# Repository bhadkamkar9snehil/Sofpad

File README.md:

# Sofpad

**A wireless, split-layout mechanical keyboard in one piece: two Sofle RGB boards in an Alice-style tilted case, with a trackpad between the thumbs, one screen and one battery.**

## What it is

Sofpad is a keyboard for the sofa and the desk. Two original [Sofle RGB](https://github.com/josefadamcik/SofleKeyboard) PCBs sit in a single printed shell, each tilted 12° like an Alice keyboard, so your hands rest naturally and the keyboard stays one object you can carry and lay on your lap. Between the thumb clusters sits a large trackpad that either thumb reaches, so the mouse never needs a separate hand movement.

One controller scans both halves. It talks to the computer over **USB-C cable or Bluetooth**, your choice at any time. The case is designed to look at home in a living room, and to be clean and serviceable on the inside: everything except the key boards rides on one removable plate.

## Features

| | |
|---|---|
| **Layout** | Sofle RGB, 30 keys per half, tilted 12° per half in an Alice-style plan, flat vertically |
| **Switches** | Cherry MX style, hot-swap |
| **Pointing** | Azoteq TPS65 trackpad, 65 × 49 mm, centre front between the thumbs |
| **Controls** | Two rotary encoders |
| **Screen** | One 2.0 in IPS display (centre rear) replaces the two small OLEDs |
| **Connectivity** | USB-C HID and Bluetooth LE HID, both always available |
| **Feel** | Haptic feedback on the trackpad (DRV2605L + LRA) |
| **Power** | One protected 1100 mAh LiPo, USB-C charging, power switch, wake on lift (LIS3DH) |
| **Controller** | One nRF52840 carrier board; the two original Pro Micro boards are removed |
| **Case** | 383 × 153 × 17.1 mm printed shell, one set of screws opens it, no paint |
| **Software** | ZMK firmware. No PC app is ever required |

## Status

Hardware design is complete and being finished for ordering. Nothing is built or tested yet.

| Area | State |
|---|---|
| Case CAD | Done. Automated checks pass: no part overlaps, everything fits its cavity, shell and plate are single solids, meshes are closed |
| Schematics | Carrier and both adapters generated, ERC clean |
| PCB layout | Carrier and both adapters routed. DRC: 0 errors, 0 unconnected |
| Verification without hardware | Schematic, layout and generator netlists agree. Every key, encoder and ground path traced from the Sofle PCB to the nRF52840 GPIO. Power, divider and bus values checked against datasheet formulas. See [ARCHITECTURE.md](hardware/r3/ARCHITECTURE.md) |
| Bill of materials | Done, India sourcing, about ₹5,156 in parts (some prices are estimates) |
| Fabrication | Fab files exported for the carrier and both adapters (`hardware/r3/pcb/fab`). Quotes and orders not placed |
| Firmware | Not started (ZMK) |
| Bench test | Months away, after hardware is ordered and built |

This is a development project, not a tested product.

## Gallery

Keycaps, knobs, battery, carrier and trackpad are fit-check envelopes. The shell, PCB outlines, key positions and mount holes are real geometry. Renders are in [docs/images](docs/images/).

## How it works

```mermaid
flowchart TB
  subgraph CASE["One-piece Sofpad enclosure"]
    L["Left Sofle RGB PCB<br/>30 keys + encoder"] --> A["Left adapter"]
    R["Right Sofle RGB PCB<br/>30 keys + encoder"] --> B["Right adapter"]
    A -->|"16-pin FFC"| MCU["nRF52840 carrier PCB"]
    B -->|"16-pin FFC"| MCU
    PAD["Azoteq TPS65 trackpad"] -->|"I2C"| MCU
    SCR["2.0 in IPS screen"] -->|"SPI"| MCU
    CELL["Protected LiPo"] --> PWR["Charger + 3.3 V buck"]
    USBC["USB-C"] --> PWR
    PWR --> MCU
  end
  MCU -->|"USB HID"| HOST["Computer"]
  MCU -.->|"BLE HID"| HOST
```

Each Sofle half keeps its keys, diodes and encoder. A small adapter solders into the old Pro Micro position and brings the matrix out on a 16-way flat cable to the single carrier board, which holds the MCU, charger, regulator, haptics driver, accelerometer and the screen and trackpad connectors. Power follows the sleep design in [ARCHITECTURE.md](hardware/r3/ARCHITECTURE.md): idle current of a few microamps, wake on key press or lift.

## Repository guide

| You want | Go to |
|---|---|
| Engineering specification | [hardware/r3/ARCHITECTURE.md](hardware/r3/ARCHITECTURE.md) |
| Parts and prices | [BOM.md](hardware/r3/BOM.md) · [BOM.csv](hardware/r3/BOM.csv) |
| PCB sources and fab export | [hardware/r3/pcb](hardware/r3/pcb/) (`carrier.py`, `adapter.py`, `build_pcb.py`, `fab_export.py`) |
| Case CAD and checks | [cad/r3](cad/r3/): [Sofpad_R3_Alice.scad](cad/r3/Sofpad_R3_Alice.scad), `check_design.py`, [DESIGN_RULES.md](cad/r3/DESIGN_RULES.md) |
| Renders | [docs/images](docs/images/) |
| Earlier concepts | [R1](cad/r1/), [R2](cad/r2/), [original source package](archives/Sofpad_All_Source_Files.zip) |

### Build it

Tools: OpenSCAD nightly (Manifold backend), KiCad 10, Freerouting 2.5 with Java 25, Blender 5.

```text
python cad/r3/check_design.py                  case checks, must print PASS
python hardware/r3/pcb/erc.py carrier          schematic check
python hardware/r3/pcb/build_pcb.py carrier    place and route (KiCad's Python)
python hardware/r3/pcb/drc.py carrier carrier  design rule check
python hardware/r3/pcb/fab_export.py carrier carrier   Gerbers, drill, placement, BOM, zip
```

Order settings (layers, mask, finish, assembly) are in the Manufacturing section of [ARCHITECTURE.md](hardware/r3/ARCHITECTURE.md). The case prints in one piece on a large FDM printer, unpainted.

## Remaining work

1. Collect quotes (JLCPCB and Indian fabs) from the exported fab files, then order boards and case.
2. Print a small fit-test piece, then the full shell.
3. Confirm the trackpad flex pitch when the part arrives (both breakout boards are on the BOM).
4. Firmware: ZMK board definition, matrix, encoders, USB and Bluetooth, trackpad gestures, haptics, wake on lift, screen.
5. Deferred: hinged tenting lift, host data on the screen over Bluetooth, over-the-air updates, optional PC companion app.

## History and source integrity

R1 (couch case) and R2 (TPS43 unibody) are kept as earlier concepts. The original ZIP is the authoritative source package: a manual file upload once flattened its folders and left 14 zero-byte files, so use the archive when you need an exact original.

## License

The Sofle RGB PCB is licensed by its author, see [LICENSE-SOFLE.txt](LICENSE-SOFLE.txt). Project license: [LICENSE](LICENSE).

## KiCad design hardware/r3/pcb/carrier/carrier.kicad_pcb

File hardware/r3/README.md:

# Sofle RGB couch keyboard — single nRF52840, single battery, Azoteq TPS65 I2C

Engineering package R3 · 9 November 2026

## What is designed

- Both original Sofle RGB PCB halves remain in one printed upper shell.
- Both existing ATmega32U4 Pro Micro boards are removed. Each socket receives a **passive adapter**.
- Two internal 16-way flex cables connect the adapters to **one** nRF52840 carrier PCB.
- Both halves share five row inputs. Each half keeps six separate column outputs and two encoder signals.
- One **Azoteq TPS65-201A-S** 65 × 49 mm I2C trackpad sits in the centre of the case between the thumb clusters.
- One protected 1100 mAh LiPo supplies the complete unit through a 3.3 V regulator.
- The charger and USB HID data share one rear USB-C port. A rear switch controls regulator enable.
- One MCU firmware image will provide Windows USB and BLE keyboard/mouse HID.

The source KiCad PCB was checked. The wiring architecture is feasible with one nRF52840 module. **Custom PCBs, charge-current values, antenna layout, and mechanical fit of purchased components require further engineering. This package is not fabrication-ready.**

## Package contents

| File | Purpose |
|---|---|
| `ELECTRICAL_REVIEW.md` | Datasheet check of the electronics, trackpad choice, open risks |
| `ARCHITECTURE.md` | Existing PCB nets, FFC wire table, MCU pin map, TPS43 I2C pins, charging path, engineering gates |
| `BOM.md` | Source-linked parts list with exact manufacturer numbers and India prices |
| `BOM.csv` | Machine-readable component quantities, prices, and status |
| `verify_matrix.py` | Source KiCad net/pad checker (uses KiCad `pcbnew`) |
| `source_pinmap.json` | Output of KiCad net verification |
| `reference/Sofle_RGB/PCB/SofleKeyboard.kicad_pcb` | Exact upstream source PCB used for the verification |
| `cad/Sofpad_R3_Alice.scad` | Editable parametric case geometry |
| `cad/sofle_rgb_geometry.scad` | Source-derived Sofle switch and mounting positions |
| `cad/sofle_components.scad` | Source-derived board footprint and component reference points |
| `cad/Unibody_Shell.stl` | Preliminary continuous upper shell for 3D printing |
| `cad/Service_Bottom.stl` | Preliminary removable bottom cover |
| `cad/TPS43_Retainer.stl` | **Obsolete** round Cirque retaining plate. Redo for the TPS43. |
| `cad/layout_components.json` | Key/encoder positions for illustration |
| `cad/render_blender.py` | Code-native Blender rendering of CAD and illustrative keycaps |
| `cad/render_*.png` | Concept images rendered from the actual STL geometry |
| `cad/verify_stl.py` | Checks that all three exported STL triangle meshes are closed |
| `LICENSE-SOFLE.txt` | Upstream license for included PCB and derived case geometry |

## Build state

**Verified:** source PCB matrix, pad nets, two encoder signal pairs, module pin budget, selected trackpad communication type, exact listed core part numbers, and exported preliminary shell geometry. The three STL files passed a closed-mesh edge check.

**Not verified:** actual left/right PCB socket orientation, folded FFC routing/contact orientation, USB-C connector alignment, printed tolerances, trackpad retention/notches, selected cell's protected dimensions and charge current, RF performance, firmware, and charger safety.

RGB LEDs and OLED displays remain off in this low-power first revision. The source PCB has not been cut or rewired. The battery charger, USB, and nRF require **new carrier PCB circuitry**; the old Pro Micro boards cannot provide wireless service.

## Print and fit procedure

1. Open `cad/Sofpad_R3_Alice.scad` in OpenSCAD.
2. Adjust dimensions after measuring the purchased trackpad and cell.
3. Export each `part`: `shell`, `bottom`, and `trackpad_frame`.
4. Print a local trackpad, USB-C, and switch fit sample first.
5. Test switch alignment, PCB mounting, and access before printing the complete shell.

The main upper shell is about **390 × 136 mm**. It needs a large-format print bed or a printing service with sufficient build area and margin.

Source project: https://github.com/josefadamcik/SofleKeyboard

PCB commit used: `fb294f7c58d0f91c379a9ef339159d4d056643e9`.

The case is based on the open Sofle PCB geometry. Preserve upstream license attribution when you share adapted files.

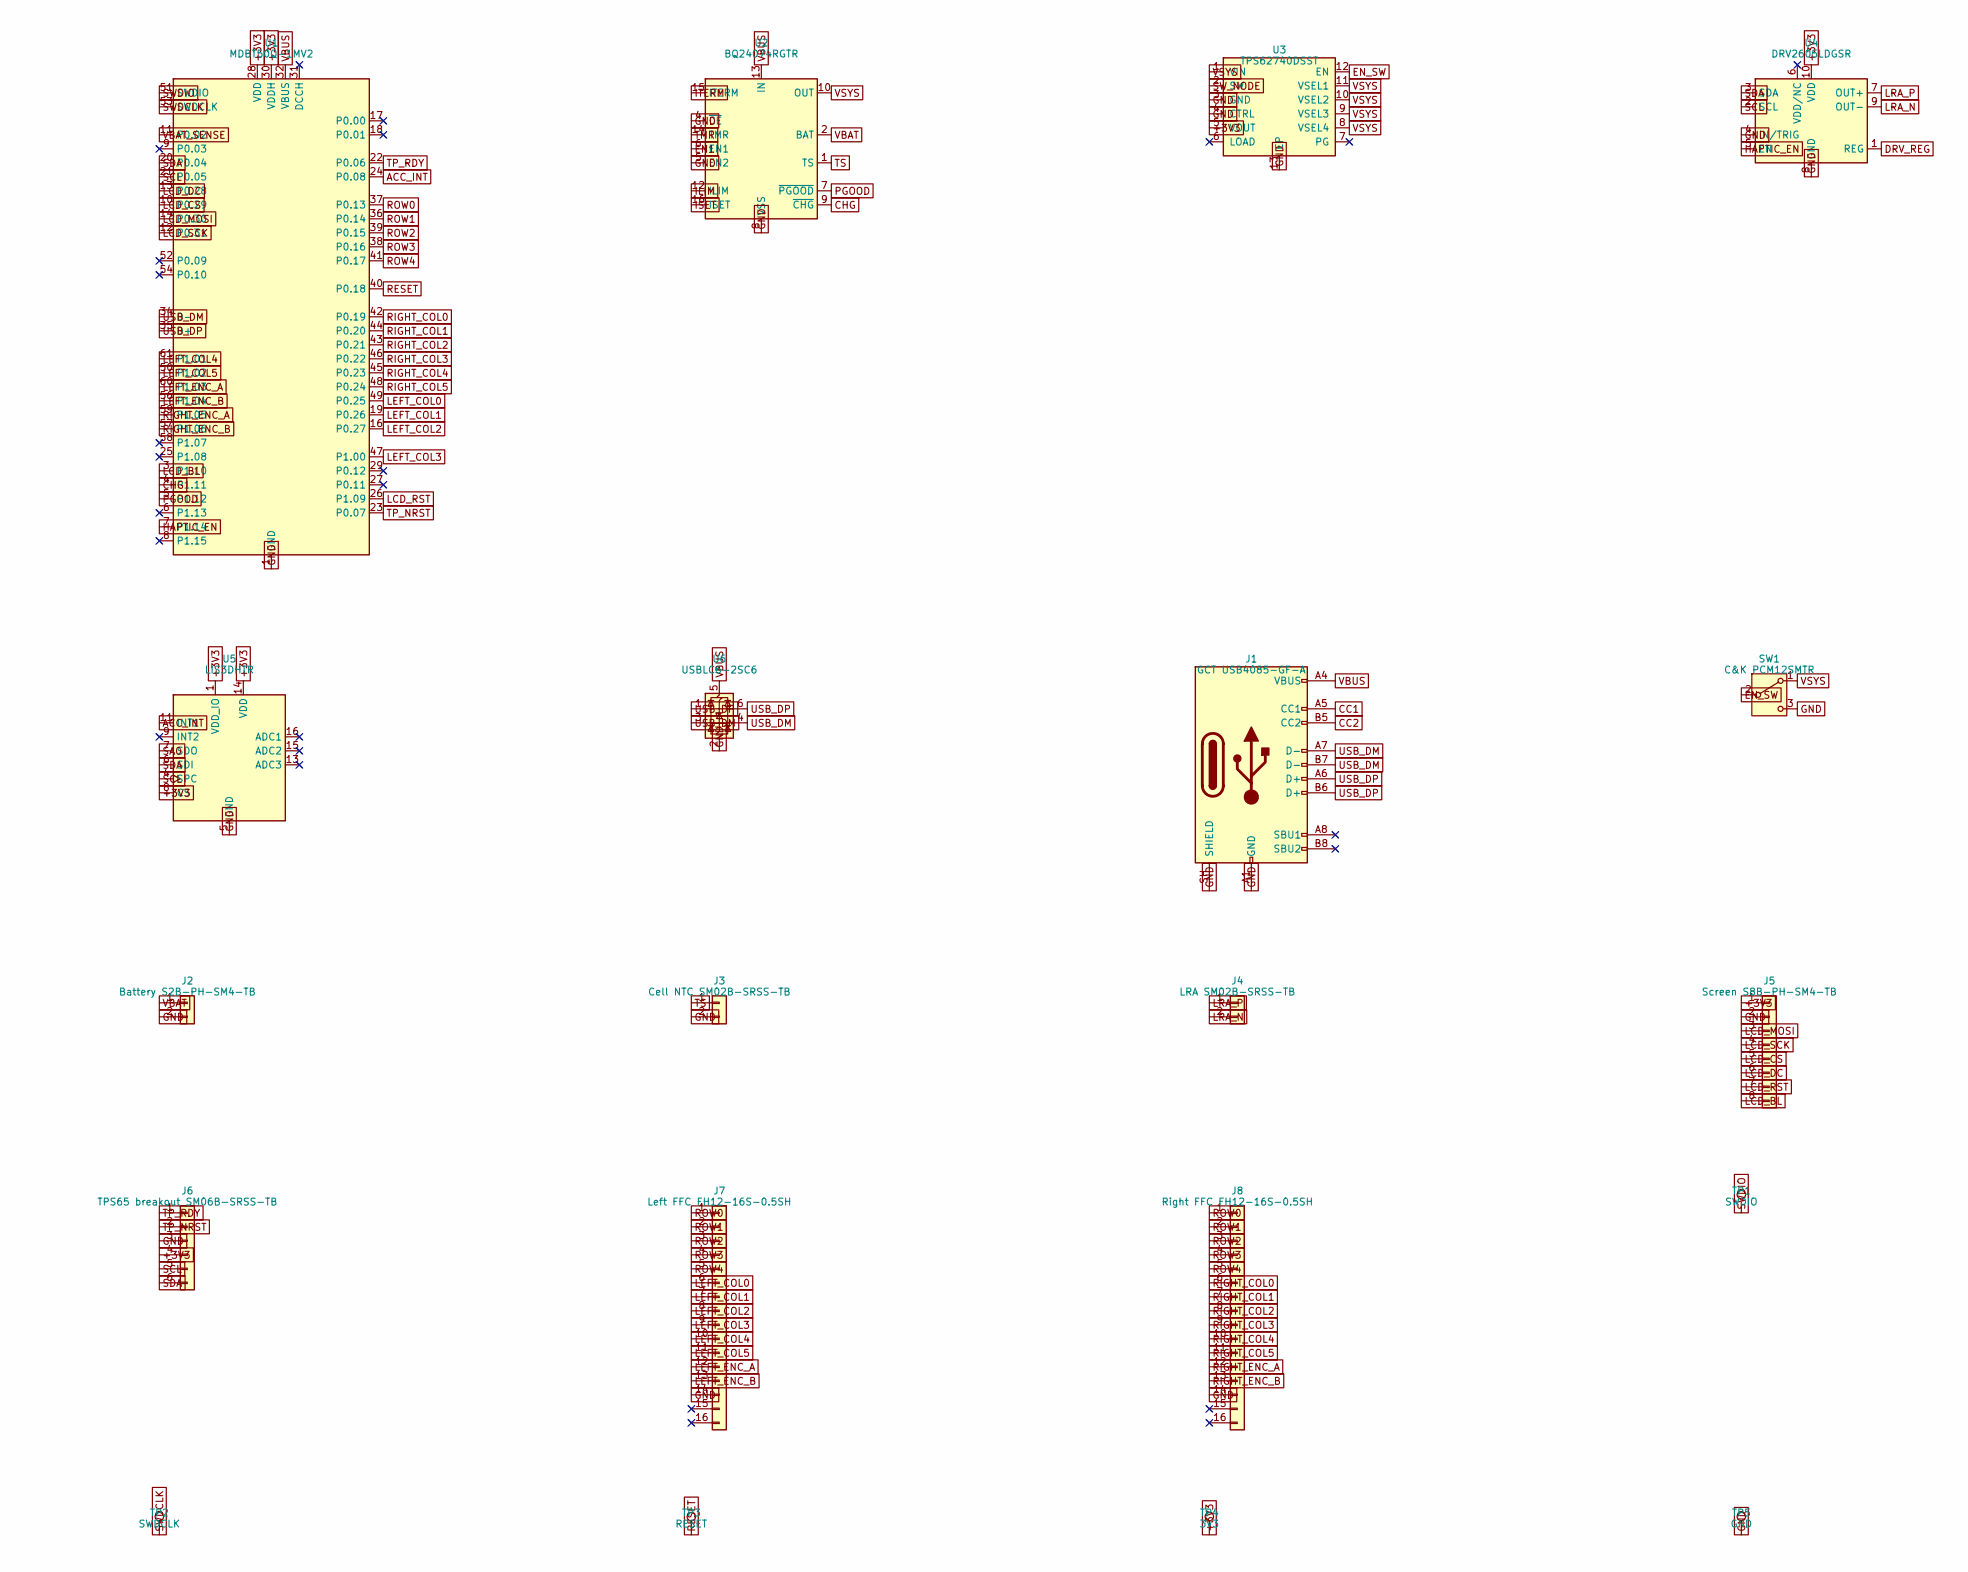
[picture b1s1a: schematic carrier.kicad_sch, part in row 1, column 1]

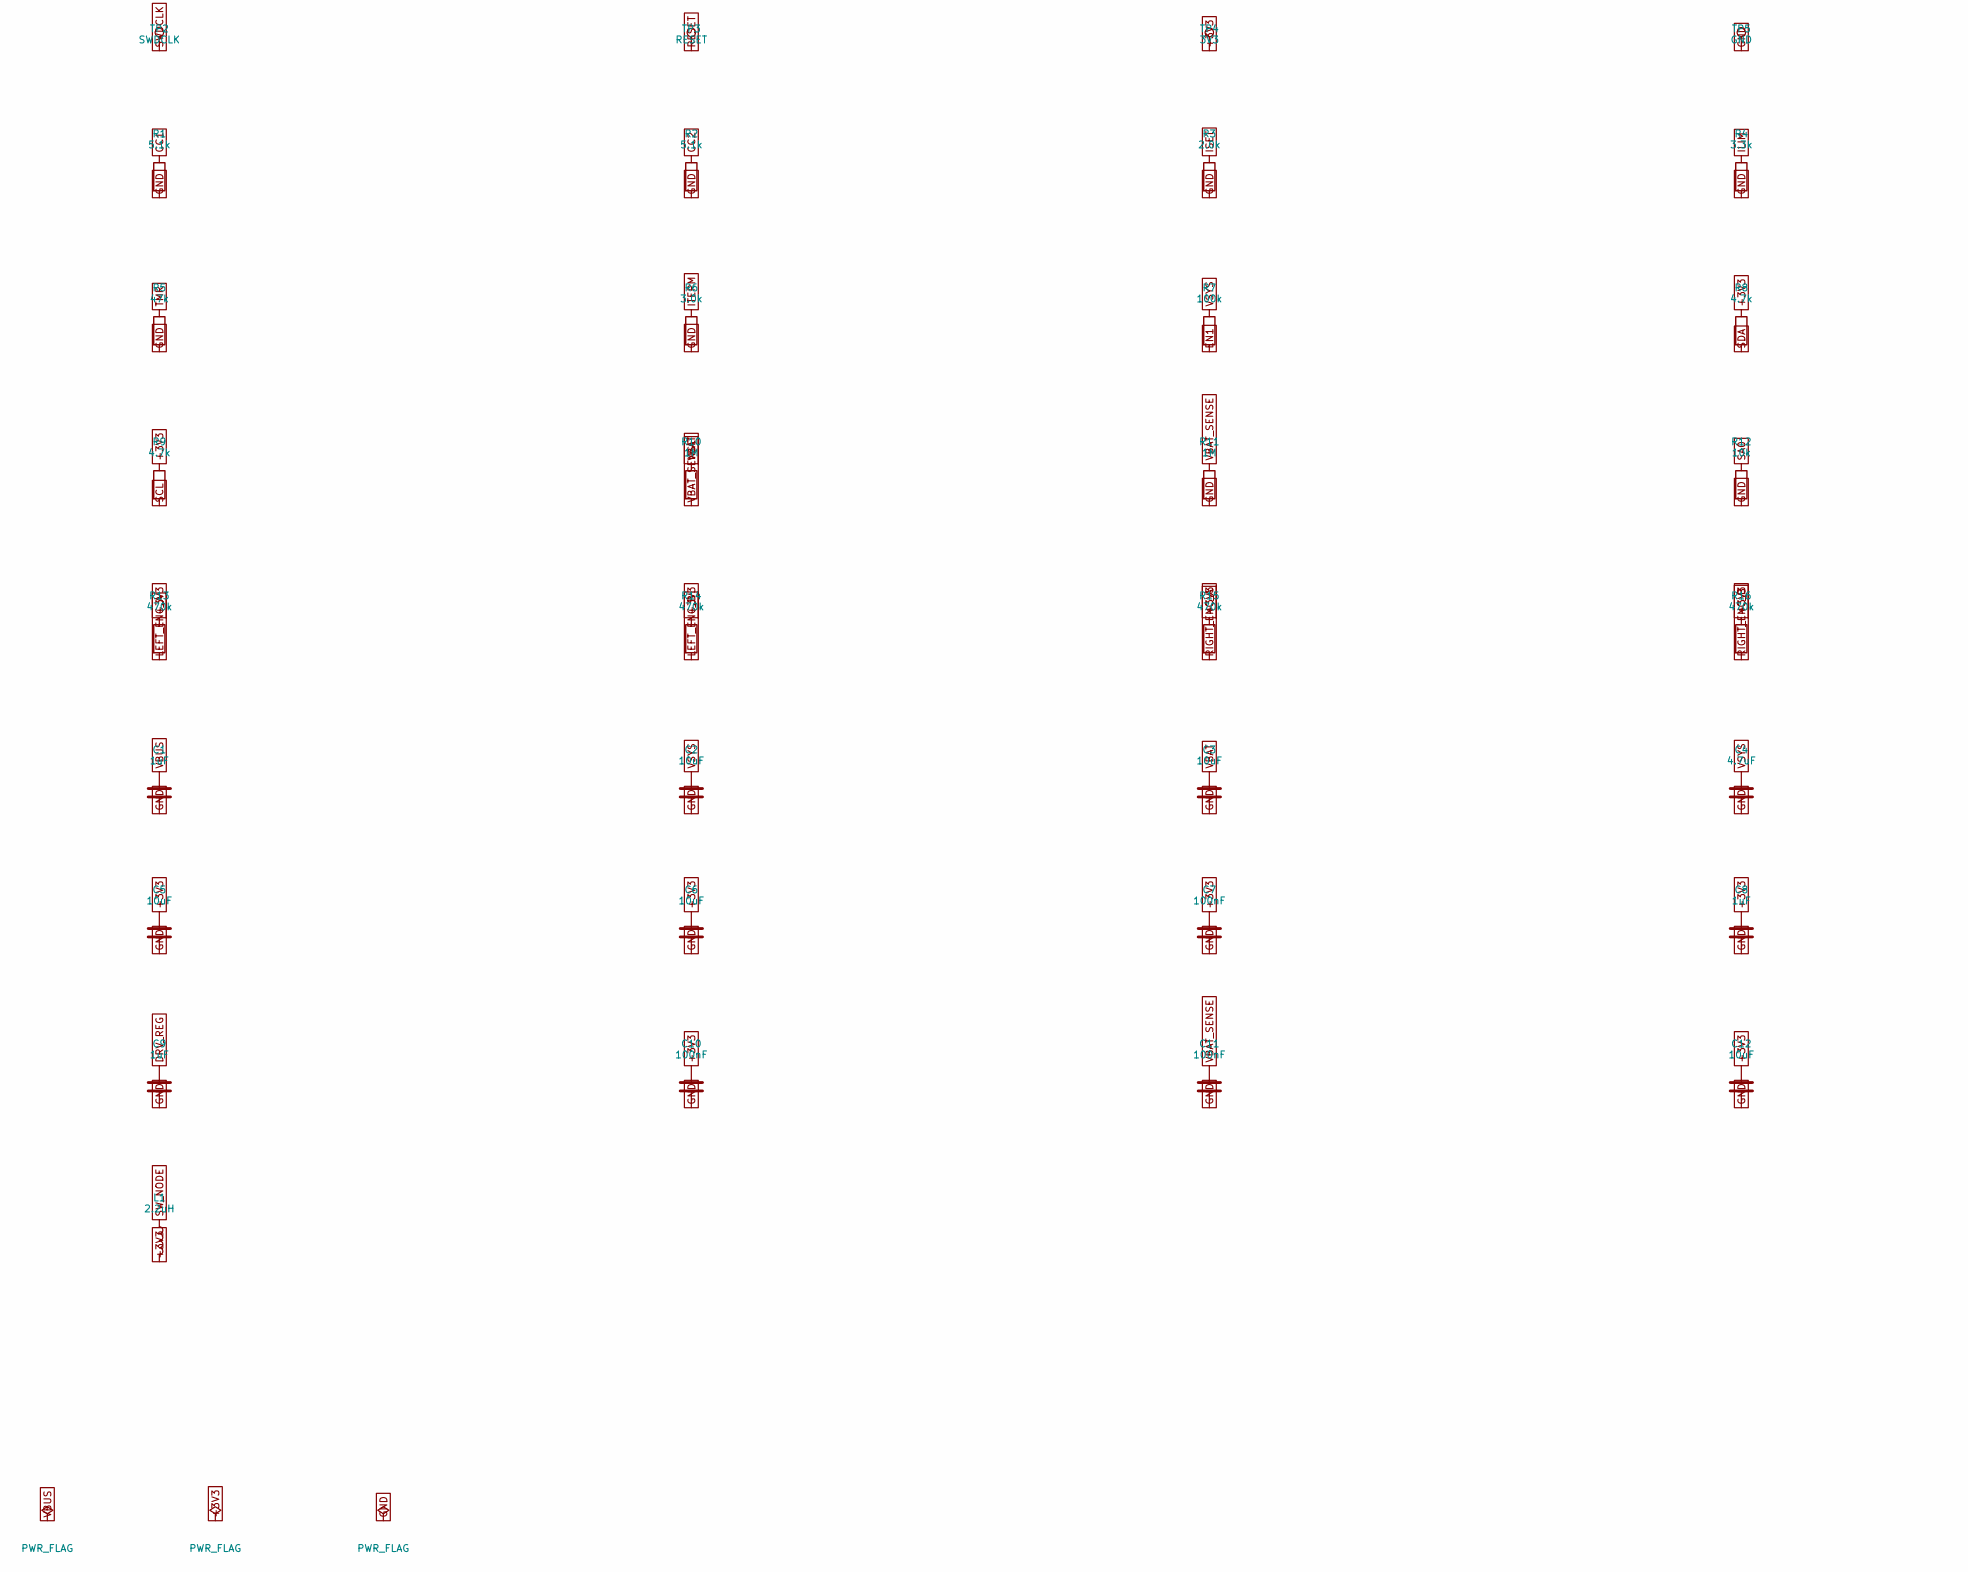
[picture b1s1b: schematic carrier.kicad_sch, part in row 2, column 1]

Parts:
C1, C8, C9: 1uF; C_0402_1005Metric
C2, C3, C5, C6, C12: 10uF; C_0603_1608Metric
C4: 4.7uF; C_0603_1608Metric
C7, C10, C11: 100nF; C_0402_1005Metric
J1: GCT USB4085-GF-A; USB_C_Receptacle_GCT_USB4085
J2: Battery S2B-PH-SM4-TB; JST_PH_S2B-PH-SM4-TB_1x02-1MP_P2.00mm_Horizontal
J3: Cell NTC SM02B-SRSS-TB; JST_SH_SM02B-SRSS-TB_1x02-1MP_P1.00mm_Horizontal
J4: LRA SM02B-SRSS-TB; JST_SH_SM02B-SRSS-TB_1x02-1MP_P1.00mm_Horizontal
J5: Screen S8B-PH-SM4-TB; JST_PH_S8B-PH-SM4-TB_1x08-1MP_P2.00mm_Horizontal
J6: TPS65 breakout SM06B-SRSS-TB; JST_SH_SM06B-SRSS-TB_1x06-1MP_P1.00mm_Horizontal
J7: Left FFC FH12-16S-0.5SH; Hirose_FH12-16S-0.5SH_1x16-1MP_P0.50mm_Horizontal
J8: Right FFC FH12-16S-0.5SH; Hirose_FH12-16S-0.5SH_1x16-1MP_P0.50mm_Horizontal
L1: 2.2uH; L_0805_2012Metric
R1, R2: 5.1k; R_0402_1005Metric
R3: 2.0k; R_0402_1005Metric
R4: 3.3k; R_0402_1005Metric
R5: 47k; R_0402_1005Metric
R6: 3.0k; R_0402_1005Metric
R7: 100k; R_0402_1005Metric
R8, R9: 4.7k; R_0402_1005Metric
R10, R11: 1M; R_0402_1005Metric
R12: 10k; R_0402_1005Metric
R13, R14, R15, R16: 470k; R_0402_1005Metric
SW1: C&K PCM12SMTR; SW_SPDT_PCM12
TP1: SWDIO; TestPoint_Pad_D1.0mm
TP2: SWDCLK; TestPoint_Pad_D1.0mm
TP3: RESET; TestPoint_Pad_D1.0mm
TP4: 3V3; TestPoint_Pad_D1.0mm
TP5: GND; TestPoint_Pad_D1.0mm
U1: MDBT50Q-1MV2; Raytac_MDBT50Q
U2: BQ24074RGTR; VQFN-16-1EP_3x3mm_P0.5mm_EP1.6x1.6mm
U3: TPS62740DSST; WSON-12-1EP_3x2mm_P0.5mm_EP1x2.65
U4: DRV2605LDGSR; MSOP-10_3x3mm_P0.5mm
U5: LIS3DHTR; LGA-16_3x3mm_P0.5mm_LayoutBorder3x5y
U6: USBLC6-2SC6; SOT-23-6

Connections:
+3V3: C5.1, C6.1, C7.1, C8.1, C10.1, C12.1, J5.1, J6.4, L1.2, R8.1, R9.1, R13.1, R14.1, R15.1, R16.1, TP4.1, U1.28 (VDD), U1.30 (VDDH), U3.5 (VOUT), U4.10 (VDD), U5.1 (VDD_IO), U5.8 (CS), U5.14 (VDD)
ACC_INT: U1.24 (P0.08), U5.11 (INT1)
CC1: J1.A5 (CC1), R1.1
CC2: J1.B5 (CC2), R2.1
CHG: U1.4 (P1.11), U2.9 (~CHG)
DRV_REG: C9.1, U4.1 (REG)
EN1: R7.2, U2.6 (EN1)
EN_SW: SW1.2 (B), U3.12 (EN)
GND: C1.2, C2.2, C3.2, C4.2, C5.2, C6.2, C7.2, C8.2, C9.2, C10.2, C11.2, C12.2, J1.A1 (GND), J1.A12 (GND), J1.B1 (GND), J1.B12 (GND), J1.SH (SHIELD), J2.2, J3.2, J5.2, J6.3, J7.14, J8.14, R1.2, R2.2, R3.2, R4.2, R5.2, R6.2, R11.2, R12.2, SW1.3 (C), TP5.1, U1.1 (GND), U1.2 (GND), U1.15 (GND), U1.33 (GND), U1.55 (GND), U2.4 (~CE), U2.5 (EN2), U2.8 (VSS), U2.17 (VSS), U3.3 (GND), U3.4 (CTRL), U3.13 (EP), U4.4 (IN/TRIG), U4.8 (GND), U5.5 (GND), U5.10 (GND), U5.12 (GND), U6.2 (GND)
HAPTIC_EN: U1.7 (P1.14), U4.5 (EN)
ILIM: R4.1, U2.12 (ILIM)
ISET: R3.1, U2.16 (ISET)
ITERM: R6.1, U2.15 (ITERM)
LCD_BL: J5.8, U1.3 (P1.10)
LCD_CS: J5.5, U1.10 (P0.29)
LCD_DC: J5.6, U1.13 (P0.28)
LCD_MOSI: J5.3, U1.14 (P0.30)
LCD_RST: J5.7, U1.26 (P1.09)
LCD_SCK: J5.4, U1.12 (P0.31)
LEFT_COL0: J7.6, U1.49 (P0.25)
LEFT_COL1: J7.7, U1.19 (P0.26)
LEFT_COL2: J7.8, U1.16 (P0.27)
LEFT_COL3: J7.9, U1.47 (P1.00)
LEFT_COL4: J7.10, U1.61 (P1.01)
LEFT_COL5: J7.11, U1.50 (P1.02)
LEFT_ENC_A: J7.12, R13.2, U1.60 (P1.03)
LEFT_ENC_B: J7.13, R14.2, U1.56 (P1.04)
LRA_N: J4.2, U4.9 (OUT-)
LRA_P: J4.1, U4.7 (OUT+)
PGOOD: U1.5 (P1.12), U2.7 (~PGOOD)
RESET: TP3.1, U1.40 (P0.18)
RIGHT_COL0: J8.6, U1.42 (P0.19)
RIGHT_COL1: J8.7, U1.44 (P0.20)
RIGHT_COL2: J8.8, U1.43 (P0.21)
RIGHT_COL3: J8.9, U1.46 (P0.22)
RIGHT_COL4: J8.10, U1.45 (P0.23)
RIGHT_COL5: J8.11, U1.48 (P0.24)
RIGHT_ENC_A: J8.12, R15.2, U1.59 (P1.05)
RIGHT_ENC_B: J8.13, R16.2, U1.57 (P1.06)
ROW0: J7.1, J8.1, U1.37 (P0.13)
ROW1: J7.2, J8.2, U1.36 (P0.14)
ROW2: J7.3, J8.3, U1.39 (P0.15)
ROW3: J7.4, J8.4, U1.38 (P0.16)
ROW4: J7.5, J8.5, U1.41 (P0.17)
SA0: R12.1, U5.7 (SDO)
SCL: J6.5, R9.2, U1.21 (P0.05), U4.2 (SCL), U5.4 (SPC)
SDA: J6.6, R8.2, U1.20 (P0.04), U4.3 (SDA), U5.6 (SDI)
SWDCLK: TP2.1, U1.53 (SWDCLK)
SWDIO: TP1.1, U1.51 (SWDIO)
SW_NODE: L1.1, U3.2 (SW)
TMR: R5.1, U2.14 (TMR)
TP_NRST: J6.2, U1.23 (P0.07)
TP_RDY: J6.1, U1.22 (P0.06)
TS: J3.1, U2.1 (TS)
USB_DM: J1.A7 (D-), J1.B7 (D-), U1.34 (D-), U6.3 (I/O2), U6.4 (I/O2)
USB_DP: J1.A6 (D+), J1.B6 (D+), U1.35 (D+), U6.1 (I/O1), U6.6 (I/O1)
VBAT: C3.1, J2.1, R10.1, U2.2 (BAT), U2.3 (BAT)
VBAT_SENSE: C11.1, R10.2, R11.1, U1.11 (P0.02)
VBUS: C1.1, J1.A4 (VBUS), J1.A9 (VBUS), J1.B4 (VBUS), J1.B9 (VBUS), U1.32 (VBUS), U2.13 (IN), U6.5 (VBUS)
VSYS: C2.1, C4.1, R7.1, SW1.1 (A), U2.10 (OUT), U2.11 (OUT), U3.1 (VIN), U3.8 (VSEL4), U3.9 (VSEL3), U3.10 (VSEL2), U3.11 (VSEL1)

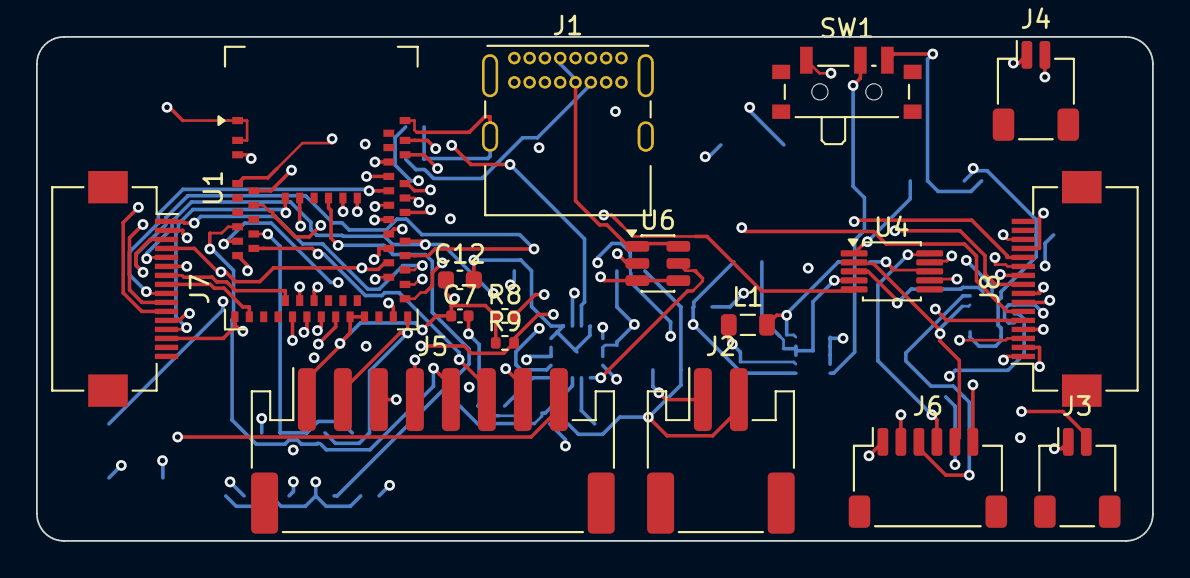
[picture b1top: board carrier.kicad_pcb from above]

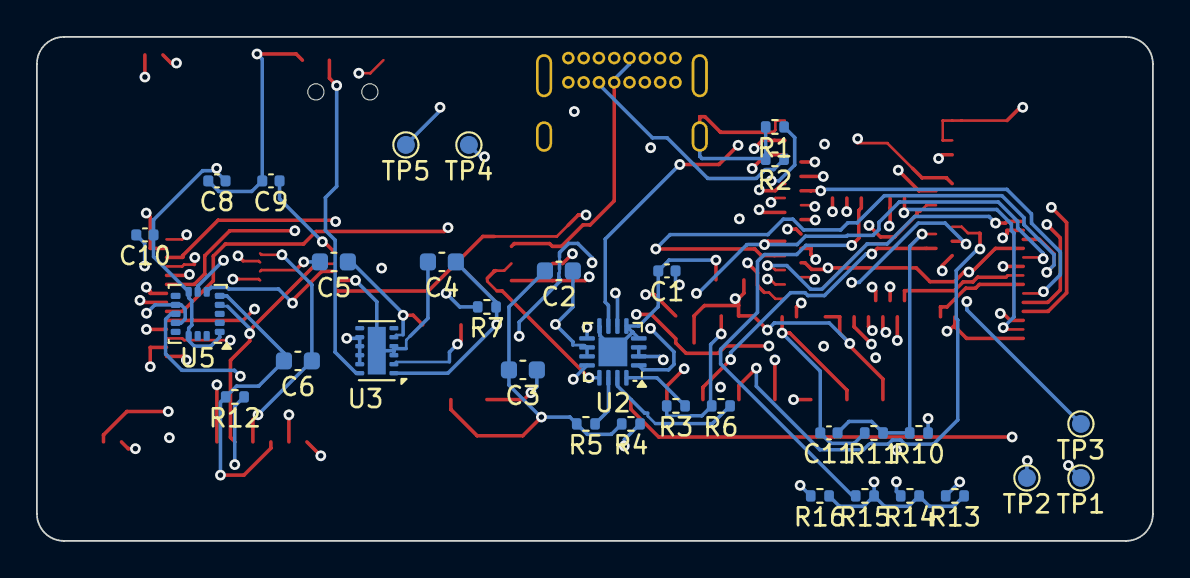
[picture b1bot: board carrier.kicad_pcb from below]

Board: 4 copper layers, 62.0 x 28.0 mm, 49 parts (32 on the bottom side), 60 nets.

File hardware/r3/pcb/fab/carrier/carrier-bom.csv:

Comment,Designator,Footprint,Quantity
100k,R7,R_0402_1005Metric,1
100nF,"C10,C11,C7",C_0402_1005Metric,3
10k,R12,R_0402_1005Metric,1
10uF,"C12,C2,C3,C5,C6",C_0603_1608Metric,5
1M,"R10,R11",R_0402_1005Metric,2
1uF,"C1,C8,C9",C_0402_1005Metric,3
2.0k,R3,R_0402_1005Metric,1
2.2uH,L1,L_0805_2012Metric,1
3.0k,R6,R_0402_1005Metric,1
3.3k,R4,R_0402_1005Metric,1
3V3,TP4,TestPoint_Pad_D1.0mm,1
4.7k,"R8,R9",R_0402_1005Metric,2
4.7uF,C4,C_0603_1608Metric,1
470k,"R13,R14,R15,R16",R_0402_1005Metric,4
47k,R5,R_0402_1005Metric,1
5.1k,"R1,R2",R_0402_1005Metric,2
BQ24074RGTR,U2,VQFN-16-1EP_3x3mm_P0.5mm_EP1.6x1.6mm,1
Battery S2B-PH-SM4-TB,J2,JST_PH_S2B-PH-SM4-TB_1x02-1MP_P2.00mm_Horizontal,1
C&K PCM12SMTR,SW1,SW_SPDT_PCM12,1
Cell NTC SM02B-SRSS-TB,J3,JST_SH_SM02B-SRSS-TB_1x02-1MP_P1.00mm_Horizontal,1
DRV2605LDGSR,U4,MSOP-10_3x3mm_P0.5mm,1
GCT USB4085-GF-A,J1,USB_C_Receptacle_GCT_USB4085,1
GND,TP5,TestPoint_Pad_D1.0mm,1
LIS3DHTR,U5,LGA-16_3x3mm_P0.5mm_LayoutBorder3x5y,1
LRA SM02B-SRSS-TB,J4,JST_SH_SM02B-SRSS-TB_1x02-1MP_P1.00mm_Horizontal,1
Left FFC FH12-16S-0.5SH,J7,Hirose_FH12-16S-0.5SH_1x16-1MP_P0.50mm_Horizontal,1
MDBT50Q-1MV2,U1,Raytac_MDBT50Q,1
RESET,TP3,TestPoint_Pad_D1.0mm,1
Right FFC FH12-16S-0.5SH,J8,Hirose_FH12-16S-0.5SH_1x16-1MP_P0.50mm_Horizontal,1
SWDCLK,TP2,TestPoint_Pad_D1.0mm,1
SWDIO,TP1,TestPoint_Pad_D1.0mm,1
Screen S8B-PH-SM4-TB,J5,JST_PH_S8B-PH-SM4-TB_1x08-1MP_P2.00mm_Horizontal,1
TPS62740DSST,U3,WSON-12-1EP_3x2mm_P0.5mm_EP1x2.65,1
TPS65 breakout SM06B-SRSS-TB,J6,JST_SH_SM06B-SRSS-TB_1x06-1MP_P1.00mm_Horizontal,1
USBLC6-2SC6,U6,SOT-23-6,1

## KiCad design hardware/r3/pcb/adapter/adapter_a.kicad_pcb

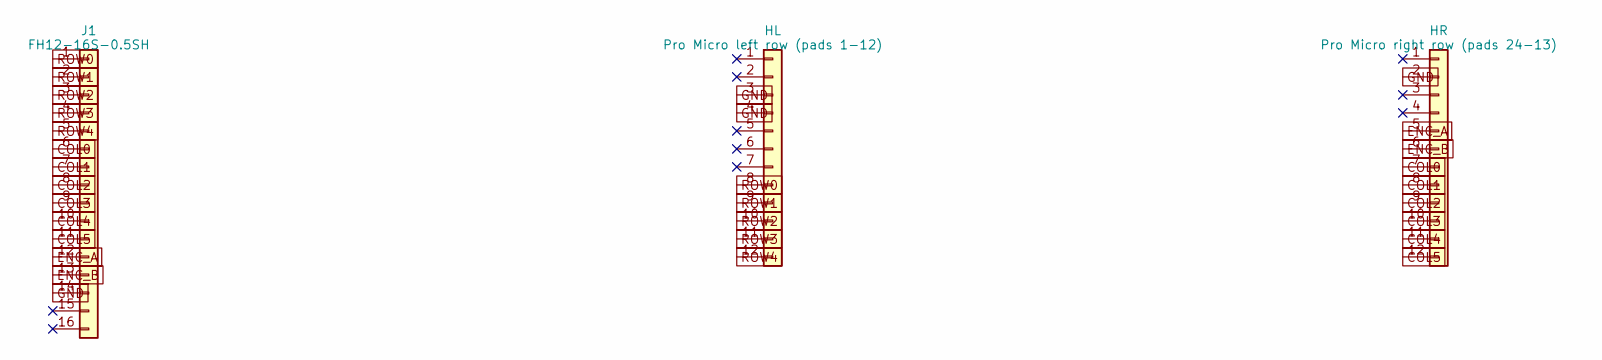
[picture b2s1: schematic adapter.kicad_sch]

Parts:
HL: Pro Micro left row (pads 1-12); PinHeader_1x12_P2.54mm_Vertical
HR: Pro Micro right row (pads 24-13); PinHeader_1x12_P2.54mm_Vertical
J1: FH12-16S-0.5SH; Hirose_FH12-16S-0.5SH_1x16-1MP_P0.50mm_Horizontal

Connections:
COL0: HR.7, J1.6
COL1: HR.8, J1.7
COL2: HR.9, J1.8
COL3: HR.10, J1.9
COL4: HR.11, J1.10
COL5: HR.12, J1.11
ENC_A: HR.5, J1.12
ENC_B: HR.6, J1.13
GND: HL.3, HL.4, HR.2, J1.14
ROW0: HL.8, J1.1
ROW1: HL.9, J1.2
ROW2: HL.10, J1.3
ROW3: HL.11, J1.4
ROW4: HL.12, J1.5

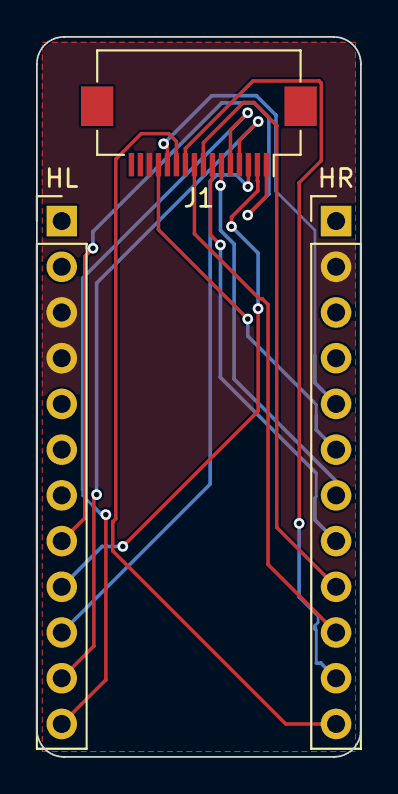
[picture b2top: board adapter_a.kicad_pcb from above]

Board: 2 copper layers, 18.0 x 40.0 mm, 3 parts (0 on the bottom side), 14 nets.

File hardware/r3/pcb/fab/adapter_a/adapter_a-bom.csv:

Comment,Designator,Footprint,Quantity
FH12-16S-0.5SH,J1,Hirose_FH12-16S-0.5SH_1x16-1MP_P0.50mm_Horizontal,1
Pro Micro left row (pads 1-12),HL,PinHeader_1x12_P2.54mm_Vertical,1
Pro Micro right row (pads 24-13),HR,PinHeader_1x12_P2.54mm_Vertical,1
